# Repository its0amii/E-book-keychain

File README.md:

# E-book keychain
### A small E-book with one word at time reading with audiobook 
I have always needed something i can read and hear stories without using my phone at all and i want it should me able to carry anywahere easily and english is my second language so i get struck on some words so i need quick access to the meaning also so i made this.
This is a small esp32 based e-book with audiobook small enough to be in a keychain:
#### Features
- one word at a time, easy and fast reading
- one click dictionary, eassy dictionary access without losing anything
- audiobook, to hear your storys
- easy file sharing, with the help of captive web

# Photo 📷

case
- 
- 
- 

# Hardware

Electronics you need:
- ESP32-C6-LCD-1.47
- CJMCU-4344 CS4344 Digital To Analog Stereo Audio Conversion Module
- 502030 500mah battry
- tactile switch smd 5x5x1.5
- 3x6x3.5MM Side Press Type SMT Tactile Push Button Switch
- some wires 

# PCB
here are the wiring and PCB digram:
- 
- 
- 
### GPIO connections

|Button|	GPIO|	Function|
|-----|-----------|-------|
|Up	|GPIO1	|Navigate Up / Increase|
|Down|GPIO2|Navigate Down / Decrease|
Left|GPIO3|Navigate left/Previous
Right|GPIO10|Navigate right /Next
OK|GPIO11|Select / Play / Pause
Power|GPIO17|Sleep / Wake
Dictionary|GPIO4|Open Dictionary
Back	|GPIO5	|Go Back

# Firmware
use platformio for uploading program to the esp32 

### Folder layout

```
frimware/
|--platformio.ini             
|--README.md                  
|--include/                   
│   |--config.h               
│   |--theme.h                
│   |--types.h                
│   |--ui.h
│   |--input.h
│   |--storage.h
   |--book_manager.h
│   |--reader.h
│   |--dictionary.h
│   |--audio_player.h
│   |--wifi_manager.h
│   |--settings.h
│   └-- User_Setup.h           
-- src                       
│   |--main.cpp              
│   |--ui.cpp
│   |--input.cpp
│   |--storage.cpp
│   |--book_manager.cpp
│   |--reader.cpp
│   |--dictionary.cpp
│   |--audio_player.cpp
│   |--wifi_manager.cpp
│   |__settings.cpp
|--scripts/
│   |__copy_user_setup.py     # platformio preuild
|__data/                     
    |--books/                 
    |__audio/ 
    |__ dict.txt/            
```

### SD card layout
```
SD root
|--books/                
│   |__#your .txt file will be here
|--audio/                # 
│   |__#your .mp3 wuill be here
|--dict.txt              
|--settings.cfg          
|--progress.cfg          
|__state.cfg             
```
# BOM (Bill of Material)
[BOM]( /doc/BOM.csv)

| item | quantity | price | link |
--------|---------|--------|---------|
|Esp32-c6-LCD|1|Rs.1135.00| [Electropi](https://www.electropi.in/waveshare-esp32-c6-147inch-display-development-board-172320-262k-color-160mhz-running-frequency-single-core-processor-supports-wifi-6-bluetooth-esp32-with-display)
|5x5x1.5mm Momentary Tactile Push Button Switch SMD| 8 | RS.80 |[Amazon](https://amzn.in/d/05bs0ZPJ)|
|3x6x3.5MM Side Press Type SMT Tactile Push Button Switch| 1| RS.5 ||
|CS4344 24Bit DAC Converter Stereo Audio Module| 1|RS.170|[Amazon](https://electropeak.com/cs4344-24bit-dac-converter-stereo-audio-module)
|502030 500mah battry|1|RS.199|https://amzn.in/d/0jcyAWPH|

``` **Note:** used ai for coding and making firmware```

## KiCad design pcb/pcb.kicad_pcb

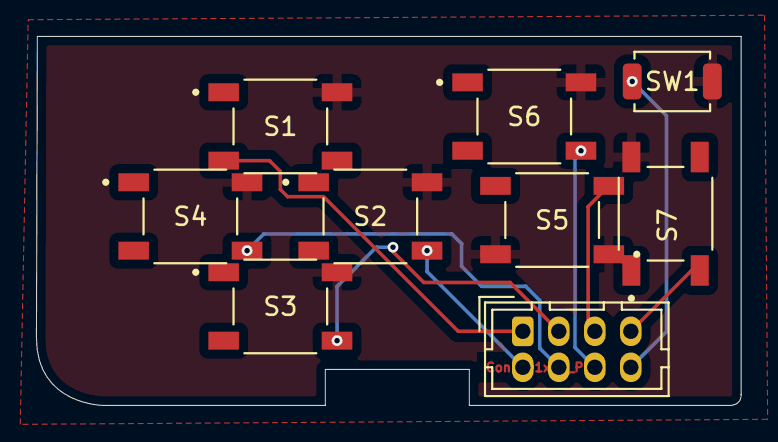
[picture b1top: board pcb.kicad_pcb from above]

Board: 2 copper layers, 39.2 x 20.5 mm, 9 parts (0 on the bottom side), 9 nets.

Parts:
J2: Conn_01x08_Pin; Hirose_DF11-8DP-2DSA_2x04_P2.00mm_Vertical
S1, S2, S3, S4, S5, S6, S7: TS18-5-15-SL-160-SMT-TR; SW_TS18-5-15-SL-160-SMT-TR
SW1: SW_SPST; SW_SPST_TS-1088-xR025

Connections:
1: J2.1, S1.3
2: J2.2, S2.4
3: J2.3, S3.4
4: J2.4, S4.4
5: J2.5, S5.3
6: J2.6, S6.4
7: J2.7, S7.3
8: J2.8, SW1.1 (A)
GND: S1.2, S2.2, S3.2, S4.2, S5.1, S5.2, S6.2, S7.1, S7.2, SW1.2 (B)
